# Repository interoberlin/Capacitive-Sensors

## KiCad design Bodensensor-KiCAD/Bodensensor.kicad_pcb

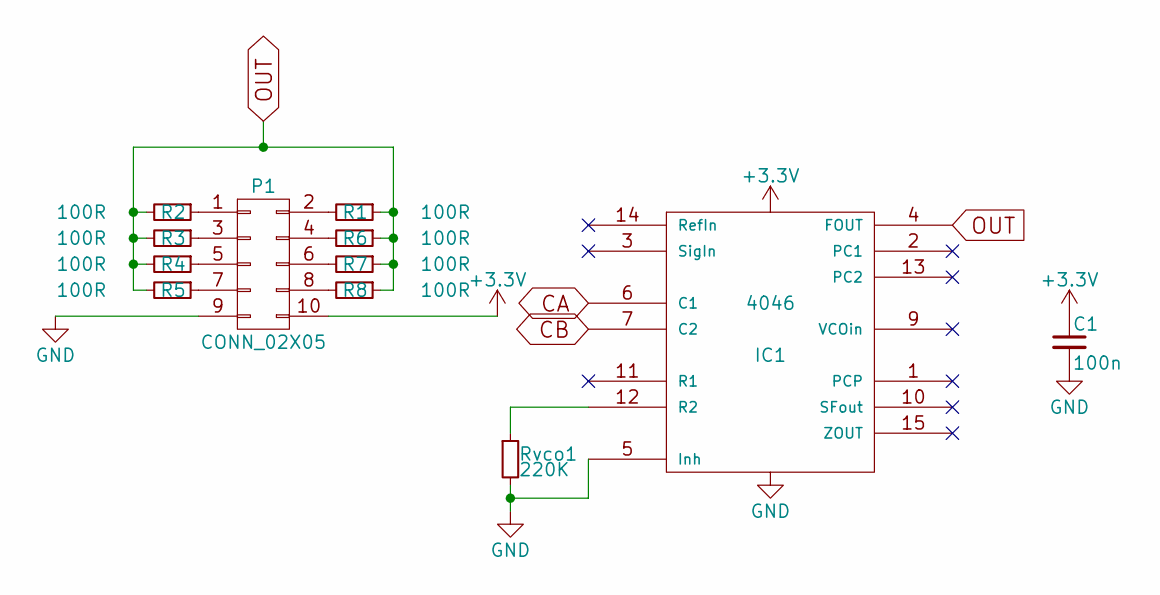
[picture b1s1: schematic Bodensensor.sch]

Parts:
C1: 100n; C_0805_HandSoldering
IC1: 4046; SO-16-N
P1: CONN_02X05; IDC_Header_Straight_10pins
R1, R2, R3, R4, R5, R6, R7, R8: 100R; R_0805_HandSoldering
Rvco1: 220K; MiniMELF_Handsoldering

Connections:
+3V3: C1.1, IC1.16 (VDD), P1.10
CA: IC1.6 (C1)
CB: IC1.7 (C2)
GND: C1.2, IC1.5 (Inh), IC1.8 (VSS), P1.9, Rvco1.2
unnamed: IC1.12 (R2), Rvco1.1
unnamed: P1.1, R2.1
unnamed: P1.2, R1.2
unnamed: P1.3, R3.1
unnamed: P1.4, R6.2
unnamed: P1.5, R4.1
unnamed: P1.6, R7.2
unnamed: P1.7, R5.1
unnamed: P1.8, R8.2
OUT: IC1.4 (FOUT), R1.1, R2.2, R3.2, R4.2, R5.2, R6.1, R7.1, R8.1

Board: 2 copper layers, 12 parts (0 on the bottom side), 12 nets, no tracks yet.

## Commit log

2016-02-16 Altium libraries as submodule
2016-02-16 starting with empty project
2016-02-16 first prototype designed and milled
2016-03-18 pulled new commits from Altium libraries; renamed Top.SchDoc to CD4046-DIP16.SchDoc
2016-03-18 began CD4046 project with onboard counter
2016-04-04 Drafted a prototype with counter and I2C address
2016-04-04 renamed folder according to last commit
2016-04-04 Prototype layout completed
2016-07-03 designed simple, new sensor with only a CD4046
2016-07-09 fabricated eight of the simple sensors
2016-08-09 VCO designed with KiCAD
2016-08-09 added 2x5 pin connector symbol
2016-08-09 annotated, footprints associated, netlist generated
2016-08-09 PCB created
2016-08-13 Revision 2 of simple SOIC-8 variant: * narrower board * resistor instead of jumper * bigger 0805 pads * corrected major connection issue
2016-08-13 Fabrication error correct: PCBs mirrored
2016-08-16 Revision 3 of simple SOIC-8 variant: * every other line wired to GND in order to reduce crosstalk * accordingly: number of signal lines reduced from 8 to 5 * adddeed second capacitor to stabilize IC 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
2016-08-19 added fabrication files of SOIC-8 variant Rev.3
2016-08-19 removed Solder and Overlay layers; updated the screenshots
2016-08-19 Revision 3.1: * larger capacitor pads * resistors on the output negatively affect signal quality
2016-08-21 updated screenshots; generated fabrication files
2016-08-28 created Multi-Nutzen with 39 PCBs
2016-08-29 created Multi-Nutzen for 6 and for 15 PCBs
2016-08-29 corrected base material size and layer set; added Multi-Nutzen files to project
